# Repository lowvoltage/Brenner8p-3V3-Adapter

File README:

EAGLE v.6 schematic and PCB layout of the Brenner8p 3.3V adapter board

Original design: http://www.sprut.de/electronic/pic/projekte/brenner8/adapter33.html

Author: Dimitar Kovachev, http://lowvoltage.wordpress.com/

Released under the Creative Commons Attribution Share-Alike 3.0 license
http://creativecommons.org/licenses/by-sa/3.0/

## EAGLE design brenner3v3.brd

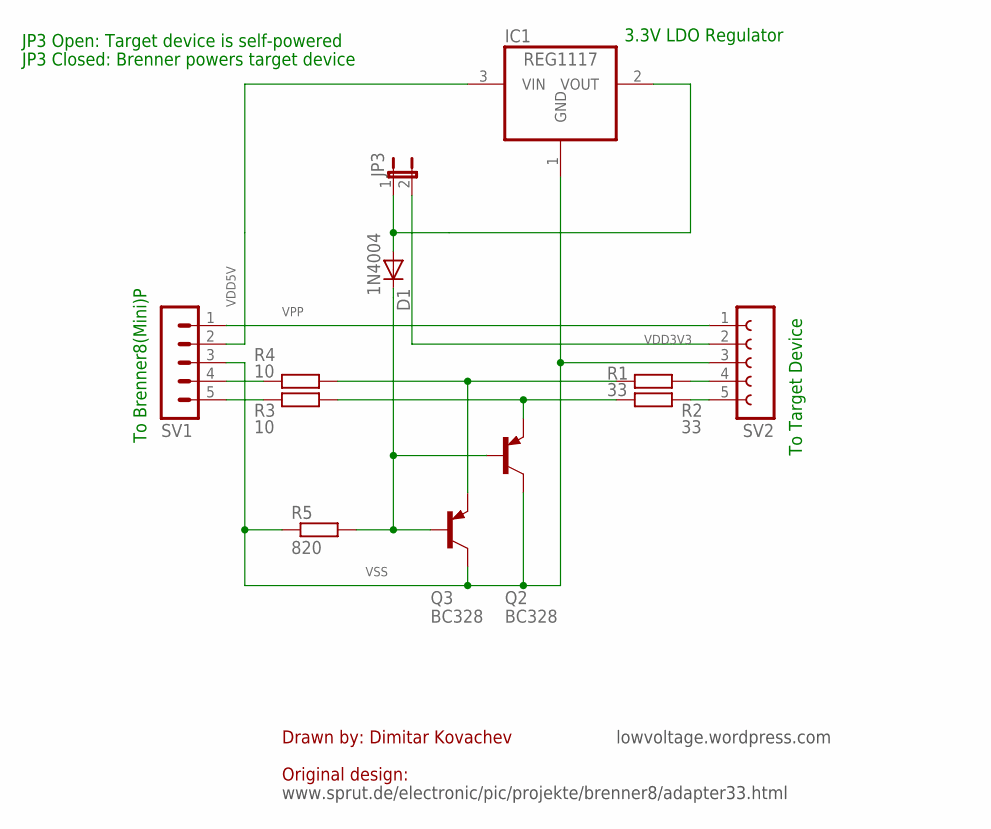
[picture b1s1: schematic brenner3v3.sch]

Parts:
D1: 1N4004; DO41-10
IC1: REG1117; SOT223
JP3: JP1E; JP1
Q2, Q3: BC328; TO92-EBC
R1, R2: 33; 0207/10
R3, R4: 10; 0207/10
R5: 820; 0207/2V
SV1: MA05-1
SV2: FE05-1

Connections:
unnamed: D1.C, Q2.B, Q3.B, R5.2
unnamed: R4.1, SV1.4
unnamed: R3.1, SV1.5
unnamed: Q3.E, R1.1, R4.2
unnamed: Q2.E, R2.1, R3.2
unnamed: R1.2, SV2.4
unnamed: R2.2, SV2.5
unnamed: D1.A, IC1.2 (VOUT), JP3.1
VDD3V3: JP3.2, SV2.2
VDD5V: IC1.3 (VIN), SV1.2
VPP: SV1.1, SV2.1
VSS: IC1.1 (GND), Q2.C, Q3.C, R5.1, SV1.3, SV2.3

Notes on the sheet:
www.sprut.de/electronic/pic/projekte/brenner8/adapter33.html
Drawn by: Dimitar Kovachev
lowvoltage.wordpress.com
Original design:
To Target Device
3.3V LDO Regulator
To Brenner8(Mini)P
JP3 Open: Target device is self-powered
JP3 Closed: Brenner powers target device

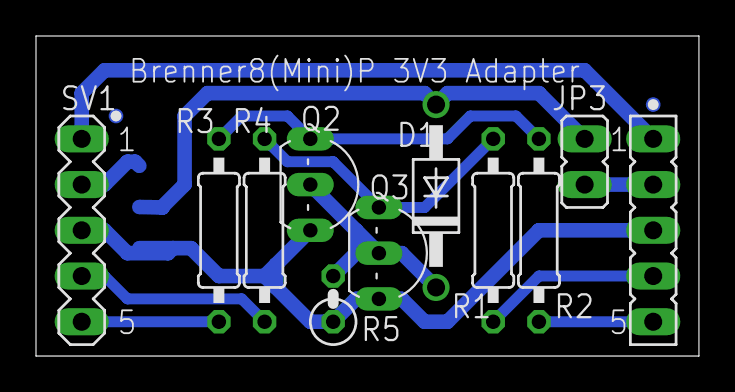
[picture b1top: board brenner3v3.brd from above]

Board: 2 copper layers, 36.8 x 17.8 mm, 12 parts (1 on the bottom side), 12 nets.

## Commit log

2012-07-07 Initial version with original schematic GIF
2012-07-08 Added schematic
2012-07-08 Added PCB
2012-07-08 Simplified schematic & layout
2012-07-08 Fixed pin-1 markings. XML cleanup
2012-07-08 Fixed pin-1 markings
2012-07-08 Added PCB description on silkscreen
2012-07-08 Metric drills
2012-07-08 Removed outer dimensions
